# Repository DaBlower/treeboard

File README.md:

# Treeboard
 <br/>
A PCB that you can use to play minigames with 4 LEDs, 4 Cherry MX switches and a XIAO RP2040. 

## Game Modes
### Reaction Tester
- **Start**: Hold the top left button for 3 seconds (the LEDs will slowly light up as you hold it)
- **How to Play**: An LED will turn on within 5 seconds, and you have to press the corresponding button as fast as possible.
### Duel
- **Start**: Hold the top right button for 3 seconds (the LEDs will slowly light up as you hold it)
- **Players**
  - Player 1 uses the left buttons and LEDs
  - Player 2 uses the right buttons and LEDs
- **How to Play**
  - Hold the PCB horizontally
  - A mirrored LED pair will light up (eg the top left and top right)
  - The first person who presses that switch wins and whoever gets to 5 wins first has their LEDs flash as celebration
### Memory Game
- **Start**: Hold the bottom left button for 3 seconds (the LEDs will slowly light up as you hold it)
- **How to Play**
  - The LEDs flash a sequence that you have to exactly recreate with the buttons
  - Each time you succeed, the length of the sequence increases
  - If you fail, the LEDs turn on and off 2 times, and if you win, they turn on one by one.
### Binary
- **Start**: Hold the bottom right button for 3 seconds (the LEDs will slowly light up as you hold it)
- **How to Play**
  - The LEDs will show a binary number for 5 seconds
  - When they turn off, you have to input that value using the keyboard
    - Pressing the top left button adds 1
    - Pressing the top right button adds 5
    - Pressing the bottom left button subtracts 1
  - To submit your number, hold the bottom right button for 2 seconds
  - If you got it correct, the LEDs will all flash twice
  - If you got it wrong, they will flash one by one 2 times

## Other features
### Idle
After 30 seconds with no input, the LEDs will play a slow idle animation

## Files
To program the XIAO RP2040, follow [this guide](https://wiki.seeedstudio.com/XIAO-RP2040-with-Arduino/) and open [this file](/firmware/treeboard/treeboard.ino) in the Arduino IDE.

## Schematic

## PCB

## BOM
* 4 Cherry MX switches
* 4 LEDs
* 4 Resistors
* 1 XIAO RP2040

made by ```@obob``` on the Hack Club Slack for the Pathfinder YSWS!

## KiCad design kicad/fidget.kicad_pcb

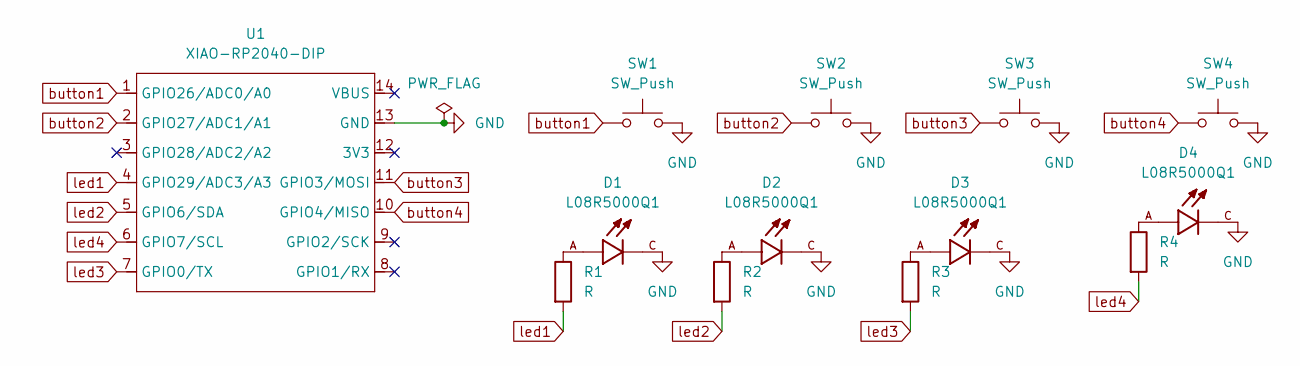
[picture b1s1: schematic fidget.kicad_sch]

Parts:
D1, D2, D3, D4: L08R5000Q1; LEDRD254W57D500H1070_3d; PARTREV NA
R1, R2, R3, R4: R; R_Axial_DIN0204_L3.6mm_D1.6mm_P5.08mm_Horizontal
SW1, SW2, SW3, SW4: SW_Push; SW_Cherry_MX_1.00u_PCB
U1: XIAO-RP2040-DIP

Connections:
GND: D1.C, D2.C, D3.C, D4.C, SW1.2, SW2.2, SW3.2, SW4.2, U1.13 (GND)
unnamed: D1.A, R1.1
unnamed: D2.A, R2.1
unnamed: D3.A, R3.1
unnamed: D4.A, R4.1
button1: SW1.1, U1.1 (GPIO26/ADC0/A0)
button2: SW2.1, U1.2 (GPIO27/ADC1/A1)
button3: SW3.1, U1.11 (GPIO3/MOSI)
button4: SW4.1, U1.10 (GPIO4/MISO)
led1: R1.2, U1.4 (GPIO29/ADC3/A3)
led2: R2.2, U1.5 (GPIO6/SDA)
led3: R3.2, U1.7 (GPIO0/TX)
led4: R4.2, U1.6 (GPIO7/SCL)

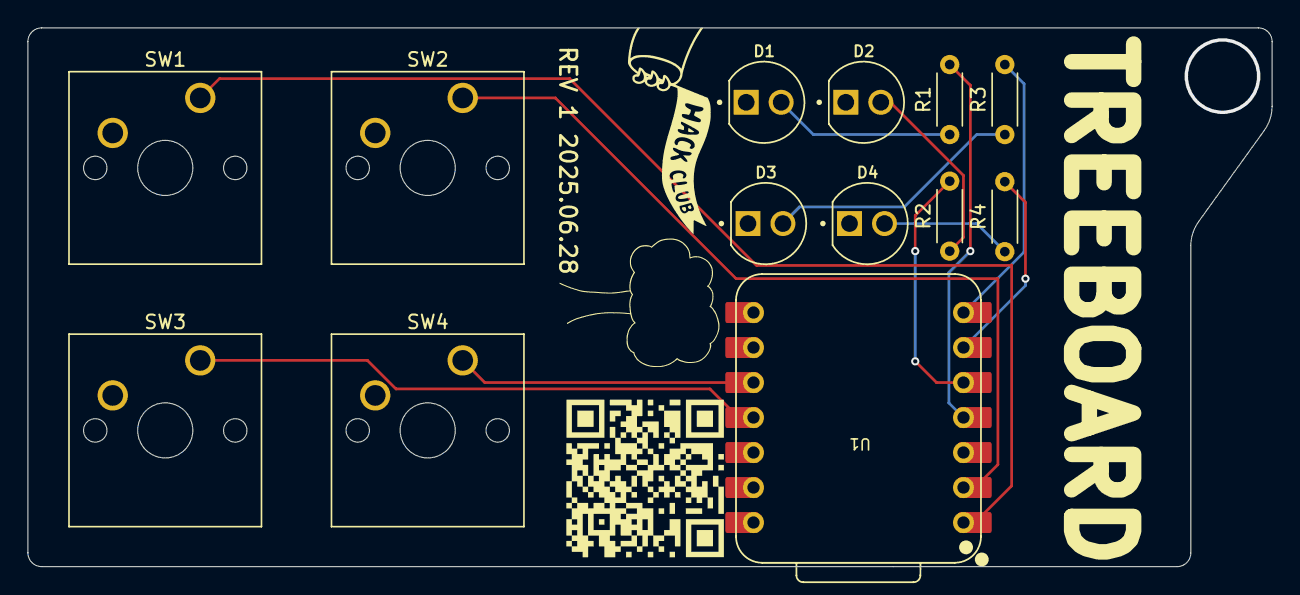
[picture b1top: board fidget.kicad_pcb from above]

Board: 2 copper layers, 90.3 x 39.1 mm, 13 parts (0 on the bottom side), 13 nets.

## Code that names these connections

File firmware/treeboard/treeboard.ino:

#define STARTUPcycles 3 // how many times does the startup loop?
#define idleTime 60000


// buttons from left to right, top to bottom
int BUT1 = D1;
int BUT2 = D9;
int BUT3 = D0;
int BUT4 = D10;
int buttons[4] = {BUT1, BUT2, BUT3, BUT4};

// Button layout (with LEDs at the top)
// 2 | 4
// 1 | 3

// LEDs from left to right, top to bottom
int LED1 = D4;
int LED2 = D5;
int LED3 = D3;
int LED4 = D6;
int leds[4] = {LED1, LED2, LED3, LED4};
int startupLeds[4] = {LED1, LED2, LED4, LED3};

// LED layout (with LEDs at the top)
// 2 | 4
// 1 | 3

int pattern[10];
int currentStep = 0;

void reaction();
void duel();
void memoryGame();
void binary();


void startup();
void ledsOff();
void idle();

// define startTime
unsigned long startTime;

// when the last input was received
unsigned long lastInput;

void setup() {
  pinMode(BUT1, INPUT);
  pinMode(BUT2, INPUT);
  pinMode(BUT3, INPUT);
  pinMode(BUT4, INPUT);

  pinMode(LED1, OUTPUT);
  pinMode(LED2, OUTPUT);
  pinMode(LED3, OUTPUT);
  pinMode(LED4, OUTPUT);
  analogWriteResolution(8);
  lastInput = millis();
  startup();
}

void loop() {
  // reaction
  if (digitalRead(BUT1) == HIGH){
    lastInput = millis();
    unsigned long pressedTime = millis();
    int currentLed = 0;
    while (digitalRead(BUT1) == HIGH){
      if (millis() - pressedTime >= 750){
        if (currentLed > 3){
          ledsOff();
          reaction();
          break;
        }
        digitalWrite(leds[currentLed], HIGH);
        currentLed++;
        pressedTime = millis();
      }
    }
  }
  // duel
  if (digitalRead(BUT2) == HIGH){
    lastInput = millis();
    unsigned long pressedTime = millis();
    int currentLed = 0;
    while (digitalRead(BUT2) == HIGH){
      if (millis() - pressedTime >= 750){
        if (currentLed > 3){
          ledsOff();
          duel();
          break;
        }
        digitalWrite(leds[currentLed], HIGH);
        currentLed++;
        pressedTime = millis();
      }
    }
  }
  // memory game
  if (digitalRead(BUT3) == HIGH){
    lastInput = millis();
    unsigned long pressedTime = millis();
    int currentLed = 0;
    while (digitalRead(BUT3) == HIGH){
      if (millis() - pressedTime >= 750){
        if (currentLed > 3){
          ledsOff();
          memoryGame();
          break;
        }
        digitalWrite(leds[currentLed], HIGH);
        currentLed++;
        pressedTime = millis();
      }
    }
  }
  // binary
  if (digitalRead(BUT4) == HIGH){
    lastInput = millis();
    unsigned long pressedTime = millis();
    int currentLed = 0;
    while (digitalRead(BUT4) == HIGH){
      if (millis() - pressedTime >= 750){
        if (currentLed > 3){
          ledsOff();
          binary();
          break;
        }
        digitalWrite(leds[currentLed], HIGH);
        currentLed++;
        pressedTime = millis();
      }
    }
  }
  // idle animation
  if (millis()-lastInput > idleTime){
    idle();
  }
}

void startup(){
  for (int i=0;i<STARTUPcycles;i++){
    for (int j=0;j<4;j++){
      digitalWrite(startupLeds[j], HIGH);
      delay(300);
    }
    for (int j=0;j<4;j++){
      digitalWrite(startupLeds[j], LOW);
    }
  }
}

void idle(){
  for (int i=0;i<4;i++){
    for (int j=15;j<160;j++){
      analogWrite(leds[i], j);
      delay(10);
    }
    for (int j=160;j>15;j--){
      analogWrite(leds[i], j);
      delay(10);
    }
  }
}

void binary(){
  randomSeed(analogRead(A2));
  int randNumber = random(15);
  startTime = millis();

  // showing binary
  for (int i=0;i<4;i++){
    digitalWrite(leds[i], (randNumber >> i) & 1); // shifts the bits of the number right by i and extracts the last bit using & 1 (which returns 0 or 1)
    delay(150);
  }
  while(millis()-startTime < 5000);
  for (int i=0;i<4;i++){
    digitalWrite(leds[i], LOW);
  }

  int count = 0;
  // input phase
  while(true){
    // top left-add 1
    if (digitalRead(buttons[0])){
      count += 1;
      delay(20); // debounce
    }
    // top right-add 5
    if (digitalRead(buttons[1])){
      count += 5;
      delay(20); // debounce
    }
    // bottom left-subtract 1
    if (digitalRead(buttons[2])){
      count -= 1;
      delay(20); // debounce
    }
    // bottom right-submit
    if (digitalRead(buttons[3])){
      startTime = millis();
      bool heldLongEnough;
      while(millis()-startTime < 2000){
        heldLongEnough = true;
        if (!digitalRead(buttons[3])){
          heldLongEnough = false;
          break;
        }
      }
      if (heldLongEnough){
        delay(1000);
        compare(count, randNumber);
        break;
      }
    }
  }
  delay(2000);
  ledsOff();
}

void compare(int c, int expected){
  if (c == expected){
    winFeedback();
  }
  else{
    failFeedback();
  }
}

void ledsOff() {
  for (int i=0; i < 4; i++){
    digitalWrite(leds[i], LOW);
  }
}

void reaction() {
  randomSeed(analogRead(A2));
  int randPin;
  int randTime;
  int time;
  for (int i = 0; i < 5; i++){ // repeat 5 times
    randPin = random(4);
    startTime = millis(); // what time did the led turn on?
    randTime = random(500,5000);
    delay(randTime);
    while (millis()-startTime < 10000){
      for (int i=0;i<4;i++){
        if (digitalRead(buttons[i]) == HIGH){ // are one of the buttons pressed
          time = millis()-startTime;
          break; // exit the for loop
        }
      }
    }
    delay(randTime);
  }

  ledsOff();

  if (time < 230){
    blink(100);
  }
  else if (time < 350){
    blink(250);
  }
  else{
    blink(400);
  }
}

void blink(int time){
  for (int i=0;i<4;i++){
    for (int j=0;j<4;j++){
      digitalWrite(leds[j], HIGH);
    }
    delay(time);
    for (int j=0;j<4;j++){
      digitalWrite(leds[j], LOW);
    }
  }
}

void duel(){
  randomSeed(analogRead(A2));
  const int maxScore = 5;
  int p1Score = 0; // player 1 is on the left
  int p2Score = 0; // player 2 is on the right
  int leftLeds[2] = {LED1, LED3};
  int rightLeds[2] = {LED2, LED4};
  while (p2Score < maxScore && p1Score < maxScore){
    int randIndex = random(2);
    delay(random(1000,4000));

    digitalWrite(leftLeds[randIndex], HIGH);
    digitalWrite(rightLeds[randIndex], HIGH);

    int winner = waitForButton(randIndex);

    digitalWrite(leftLeds[randIndex], LOW);
    digitalWrite(rightLeds[randIndex], LOW);

    if (winner == 1) p1Score++;
    else if (winner == 2) p2Score++;

    delay(500);
  }
  if (p1Score == maxScore) flashLeds(leftLeds[0], leftLeds[1]);
  else flashLeds(rightLeds[0], rightLeds[1]);

}

void flashLeds(int L1, int L2){ // flash L1 and L2
  for (int i = 0; i < 6; i++) {
    digitalWrite(L1, HIGH);
    digitalWrite(L2, HIGH);
    delay(200);
    digitalWrite(L1, LOW);
    digitalWrite(L2, LOW);
    delay(200);
  }
}


int waitForButton(int expected){
  while (true) {
    for (int i = 0; i < 4; i++) {
      if (digitalRead(buttons[i]) == HIGH) {
        while (digitalRead(buttons[i]) == HIGH);  // wait for release

        if (i == expected || i == expected + 1) { // if it is the expected led or the respective one on the other side
          return (i < 2) ? 1 : 2;  // buttons 0–1 → P1, 2–3 → P2
        } 
      }
    }
  }
}

void memoryGame(){
  currentStep = 1;
  while (true){
    generatePattern(); // create the pattern
    showPattern(); // show the pattern
    if (!getPlayerInput()){ // check if player failed
      failFeedback();
      break;
    }
    winFeedback();
    currentStep++; // increase difficulty
    delay(1000);
  }
}

void generatePattern(){
  randomSeed(analogRead(A2));
  for (int i = 0; i < currentStep; i++){
    pattern[i] = random(4);
  }
}

void showPattern(){
  for (int i = 0; i < currentStep; i++){
    int led = pattern[i];
    digitalWrite(leds[led], HIGH);
    delay(500);
    digitalWrite(leds[led], LOW);
    delay(250);
  }
}

bool getPlayerInput(){
  for (int i = 0; i < currentStep; i++){
    int expected = pattern[i];
    int pressed = waitForButtonPress();
    if (pressed != expected){
      return false;
    }
  }
  return true;
}

int waitForButtonPress(){
  while (true){
    for (int i = 0; i < 4; i++){
      if (digitalRead(buttons[i]) == HIGH){
        while (digitalRead(buttons[i]) == HIGH); // wait until button is released
        delay(50);
        return i;
      }
    }
  }
}

void failFeedback(){
  for (int i = 0; i < 2; i++){
    for (int j = 0; j < 4; j++){
      digitalWrite(leds[j], HIGH);
    }
    delay(150);
    for (int j = 0; j < 4; j++){
      digitalWrite(leds[j], LOW);
    }
    delay(150);
  }
}

void winFeedback(){
  for (int i = 0; i < 4; i++){
    digitalWrite(leds[i], HIGH);
    delay(150);
    digitalWrite(leds[i], LOW);
  }
}

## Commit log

2025-06-28 kicad init
2025-06-28 add rp2040 symbol
2025-06-28 assign footprints + add footprints and step files
2025-06-28 add 3d models
2025-06-28 update led footprint with 3d models
2025-06-28 actually add led models
2025-06-28 add xiao 3d model
2025-06-28 routing + ground plane
2025-06-28 move kicad files to their own folder
2025-06-28 first 2 games
2025-06-28 add duel and memorygame
2025-06-28 fix loop
2025-06-28 add images
2025-06-28 update silkscreen + images
2025-06-28 add more silkscreen
2025-06-28 update images
2025-06-28 add keychain hole
2025-06-28 add production files
2025-07-03 add binary game
    - The LEDs will show a binary number for 5 seconds
    - When they turn off, you have to input that value using the keyboard
    - Pressing the top left button adds 1
    - Pressing the top right button adds 5
    - Pressing the bottom left button subtracts 1
    - To submit your number, hold the bottom right button for 2 seconds
2025-07-03 update production files
2025-07-04 add startup animation and idle animation
2025-07-04 add idle description to readme
2025-07-04 add reaction time feedback and fix errors
2025-07-08 final production files
